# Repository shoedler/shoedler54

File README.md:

> Kailh Choc v2 Ice Creams, Taihao THTs

# shoedler54
A 54-key, column-staggered, ortholinear, wireless split keyboard, inspired by ZSA Voyager and silakka54.
Designed for Mx-spacing (18mm keycaps) and 1350 Choc v1 or v2 switches.

## Why?

This project came to life as I wanted to get up to speed with [ergogen.xyz](ergogen.xyz). The main goal of was to build a keyboard using solely the declarative ergogen paradigm - including making a case. As such, the only thing that was done outside of ergogen was to route the PCB and flip one case half in the slicer. That, as well as configuring the firmware (it'd be a nice extension to ergogen to generate the `.dtsi` file for ZMK automatically, but alas, that's not supported - yet).
Other things I've aimed for:
- Must be cheap, < $100 for a complete keyboard.
- Must be low profile, comparable to the ZSA Voyager.

## Impressions

> Carry case

> With optional MCU + battery cover

> Black version with Kailh Choc v2 Black Clouds, Repo-included 3D printed keycaps

---

## Bill of materials

For one complete board - e.g. two halves - you'll need:

- 2 Promicro NRF52840
- 54 1N4148W SOD-123 Diodes
- 54 Kailh Low-profile 1350 Hotswap Sockets
- 54 Keyswitches, Choc v1 or v2
- 54 1u (18mm) Keycaps, Choc v1 or v2 stems (I suggest to print the provided ones (Mx-stem e.g. Choc v2), or - if you want legends, the Taihao THTs)
- 2 EVQPUL02K Switches ($\to$ board reset button)
- 2 SSSS811101 Switches ($\to$ power switch)
- 2 801540 3.7v, 380mAh Batteries
  - or, 2 701535 3.7v, 350mAh
  - or, 2 501646 3.7v, 380mAh (these are too long (46mm) and require to be soldered to the JST pads, which I **do not recommend**!)
- 2 JST PH 2.0 THT Sockets

For the case you'll need:

- Obviously, the printed case files. See section about printing below.
- 10x M2x5 (or 6)mm flathead screws
- 10x M2x3mm Heat set inserts
- Optionally, some painters tape.

## Approximate cost

| What | Supplier | Comment | Price |
| --- | --- | --- | --- |
| 2 PCBs | JLCPCB | 5pcs. (min), including a hefty delivery fee to get to my location, $32 | ~$13 |
| 2 MCUs | AliExpress | Promicro NRF52840 | ~$4 |
| 54 Diodes | AliExpress | 1N4148W SOD-123 | ~$1 |
| 54 Kailh Low 1350 Sockets | AliExpress | Hotswap | $4 |
| 54 Keyswitches, Choc v1/v2 | AliExpress | pack of 70 | $25 |
| 54 1u Keycaps, Choc v1/v2 | AliExpress | pack of 60 | $15 |
| 2 Reset Switches | AliExpress | EVQPUL02K | ~$1 |
| 2 Power Switches | AliExpress | SSSS811101 | $1 |
| 2 Batteries | AliExpress | 801546, 380mAh | $8 |
| 2 JST PH 2.0 Sockets | AliExpress | | ~$1 |
> Prices as of january, 2026

Should result in ~$75 per completed keyboard. This does not include the case hardware and printed case files, but it's all you need to get a working keyboard. Also, the prices listed are adjusted to the amount of parts required.

> [!NOTE]
> You'd want to buy some parts in "bulk", like a strip of 100 diodes. Since you likely also have a minimum order quantity for the PCBs, it might make sense to buy two more MCUs and maybe some old keyswitches and caps to get another full keyboard out of the rest of the parts and still have one PCB for soldering mistakes left ;)

As alluded to in the BOM, a 3d printable model for a custom cap that fits this build is provided - more on that in the build guide.

## Build guide

### PCB manufacturing

> PCB related files are located in the `kicad` directory.

Assuming you have ordered the parts and don't want to route the PCB yourself, there's premade gerber archive located at `kicad/gerber.zip` which you can use. I've used JLCPCB, default settings (1.6mm two layer PCB) and with the black solder mask.

### Printing the case

> Case files are located in the `stl` directory.

I used a Babulab A1 mini and default slicer settings (Bambustudio). Everything was printed in their PLA Matte.

#### What do I need to print?

You'll need at least:

- 2x `shoedler54_switchplate_right.stl`, which is the plate that sits on the PCB and where the keyswitches are mounted into - I recommend using the provided 3mf files for that: `shoedler54_switchplate_left.3mf` and `shoedler54_switchplate_right.3mf`. That'll give you mirrored versions so you have the buildplate-finish texture on the same side for both halves.
- 2x `shoedler54_case_left.stl`, which is the case where the PCB gets mounted in - same story, use the provided 3mf files for that: `shoedler54_case_left.3mf` and `shoedler54_case_right.3mf`. That'll also give you mirrored versions for both halves with fuzzy skin. Theoretically, you don't **need** the case, but I strongly recommend it to provide a little bit of protection for the PCB. If you're working directly with the stl, then you'll have to mirror it. I suggest using the fuzzy skin setting (in Bambustudio: `Others > Special mode > Fuzzy skin`, use "Contour").

Optional:

- 2x `shoedler54_case_cover_right.stl`, which is a small cover for the MCU + battery. Use `shoedler54_case_cover_left.3mf` and `shoedler54_case_cover_right.3mf` for mirrored version. Same as with the case, if you're working with the stl directly you'll need to mirror this too.
- 1x `shoedler54_carry_case.stl`, which is a Go60-ish carry shell for the shoedler54. Use `shoedler54_carry_case.3mf` for a version with fuzzy skin. I did manage to print it without support, but there's a bit of luck involved.

### Printing the keycaps

> Keycap related files are located in the `scad` directory.

The caps require no supports if you place them on one of the fillets - they do however require good bed adhesion. This, just like the case, was also printed on a Bambulab A1 mini with PLA Matte. Also, like the case, I've provided a 3mf file to print 26 regular + 1 indexing (F/J keys on QWERTY) keys. If you have to use the stl directly:

- Use 0.12mm layer height (including the initial layer).
- Use a brim - if your slicer doesn't automatically generate it, add it manually.

> [!NOTE]
> The keycap was designed in [OpenSCAD](openscad.org). It's fully parametrized, so it's easy to adapt to your liking.

### Soldering

Since the PCB is reversible it can get confusing quick. All of the components **except the ProMicro and the JST connector** are soldered to the backside of each half.

1. Solder diodes, hotswap sockets, reset- and powerswitches on the backside of each half. **This is also the side were you bridge all of the solder-jumpers with solder** (8 for the Mcu, 2 for the Battery connector).
2. Direct-solder the ProMicro to the frontside of the PCB, along with the JST connector. (Pin Sockets are also an option for the mcu, if you want - it just makes the keyboard a bit thicker)

> [!CAUTION]
> Before you continue it's a good idea to verify that there's no short between the JSTs +/- terminal as well as the ProMicros VCC and GND.

I suggest to load the firmware next and check that everything works before assembly.

### Loading the ZMK firmware

> Firmware related files consist of: config/, boards/, zephyr/ directories, as well as the build.yml file and the GitHub Actions workflow in .github/workflows.build.yml

Get the latest firmware from https://github.com/shoelder/shoedler54/actions, select the latest run and scroll down to Artifacts - you'll be able to download the zip archive from there.

> [!NOTE]
> There'll be two .uf2 files per half in the zip archive - a `de-ch` and an `en` version. This refers to the keycode locale that's been used. I myself require a swiss locale, but, to make the default firmware more useful for more people, I've added an english version too. You can check the keymaps out in the `config/boards/shields/shoedler54` directory.

For each half:

1. Plug in the half to your device using a USB cable.
2. Press the reset button twice within 500ms - on my versions of the ProMicro, their red LED breaths gently once you've entered bootloader mode.
3. You'll see a `NICENANO` appear in your device tree. Simply drag and drop the **correct** firmware for the half your working on onto the mcu - it should eject itself automatically once the firmware is flashed.

> [!NOTE]
> If you run into trouble, there's also a `settings_reset` firmware provided in the archive. See [the ZMK troubleshooting guide](https://zmk.dev/docs/troubleshooting/connection-issues#reset-split-keyboard-procedure) on how to flash it.

### Assembly

1. Prep the cases by installing the heat set inserts.
2. Cover the bottom sides of the PCBs with tape (I used masking tape). Apply the first layer quite firmly, such that it follows the contours of the hotswap sockets. You'll want to make sure that you extend the tape over the edges of the PCB. Apply at least 3 layers. In my experience anything beyond 5 layers of standard painters tape yields no further improvements. Also, it gets thick quick.

3. Trace the PCB outline to the tape with a pen. Also, trace the screw holes.

4. Remove the tape, and cut out the shape - make sure to inset the cut about 2-3mm, so the tape is not visible when everything is assembled. For the screw holes, cut a ~5x5mm square. Apply the tape.

5. Assemble both halves.

6. Install the switches, caps and the battery. For the battery, I usually use a thin, clear double-sided tape. Done!

---

## Modifying the ergogen config

The whole point of using ergogen, is to easily adapt the PCB to your liking. So give it a go!
Modifying the config will force you to reroute the PCB again. Though fear not - using [Freerouting](www.freerouting.app) this literally takes a minute to do (including adding freerouting to KiCad), provided you have KiCad >=8 and JRE >= 17 for Freerouting already installed.

> [!NOTE]
> To add the Freerouting KiCad integration, just follow [this](https://github.com/freerouting/freerouting/blob/master/docs/integrations.md) official guide.

1. Paste `config.yml` located in `/ergogen` into [ergogen.xyz](ergogen.xyz) and download the `shoedler54.kicad_pcb` file.
2. Copy (and overwrite) `shoedler54.kicad_pcb` to the `kicad` directory of this repository *(this part is only required if you intend to keep the source of this repository up to date - e.g. if you forked this)*
3. Open the PCB in KiCad (Standalone PCB editor suffices) and click on `Tools > External Plugins > Freerouting`
4. Let it rip. In my experience, the defaults of Freerouting suffice.

> [!IMPORTANT]
> Back in KiCad, run the DRC in `Inspect > Design Rule Checker`. I usually right click `> Ignore all 'Footprint not found in libraries' violations` to ignore missing ceoloide footprint warnings. This might leave you with some warnings which you need to manually resolve. For example, i usually get "Track has unconnected end", which is easily resolved by deleting the stub.

5. `File > Plot... > Generate Drill Files`, name the folder "gerber", then press `Generate` and close that popup. Press `Plot` back in the plot dialog. Done!

## References

- Flatfootfox' detailed design guide: https://flatfootfox.com/ergogen-part1-units-points/
- nickcoutsos Keymap-editor: https://nickcoutsos.github.io/keymap-editor/
- nickcoutsos Keymap-layout-tools: https://nickcoutsos.github.io/keymap-layout-tools/
- Joel Spadins zmk-locale-generator for the de-swiss keycode header: https://github.com/joelspadin/zmk-locale-generator
- ZMK guide on how to add a new shield: https://zmk.dev/docs/development/hardware-integration/new-shield
- More of my keyboards:
  - effiddy - a 50-key wireless split, inspired by totem: https://github.com/shoedler/effiddy
  - ezy54 - A 54-key, column-staggered, wireless split keyboard, inspired by ZSA Voyager and totem: https://github.com/shoedler/ezy54

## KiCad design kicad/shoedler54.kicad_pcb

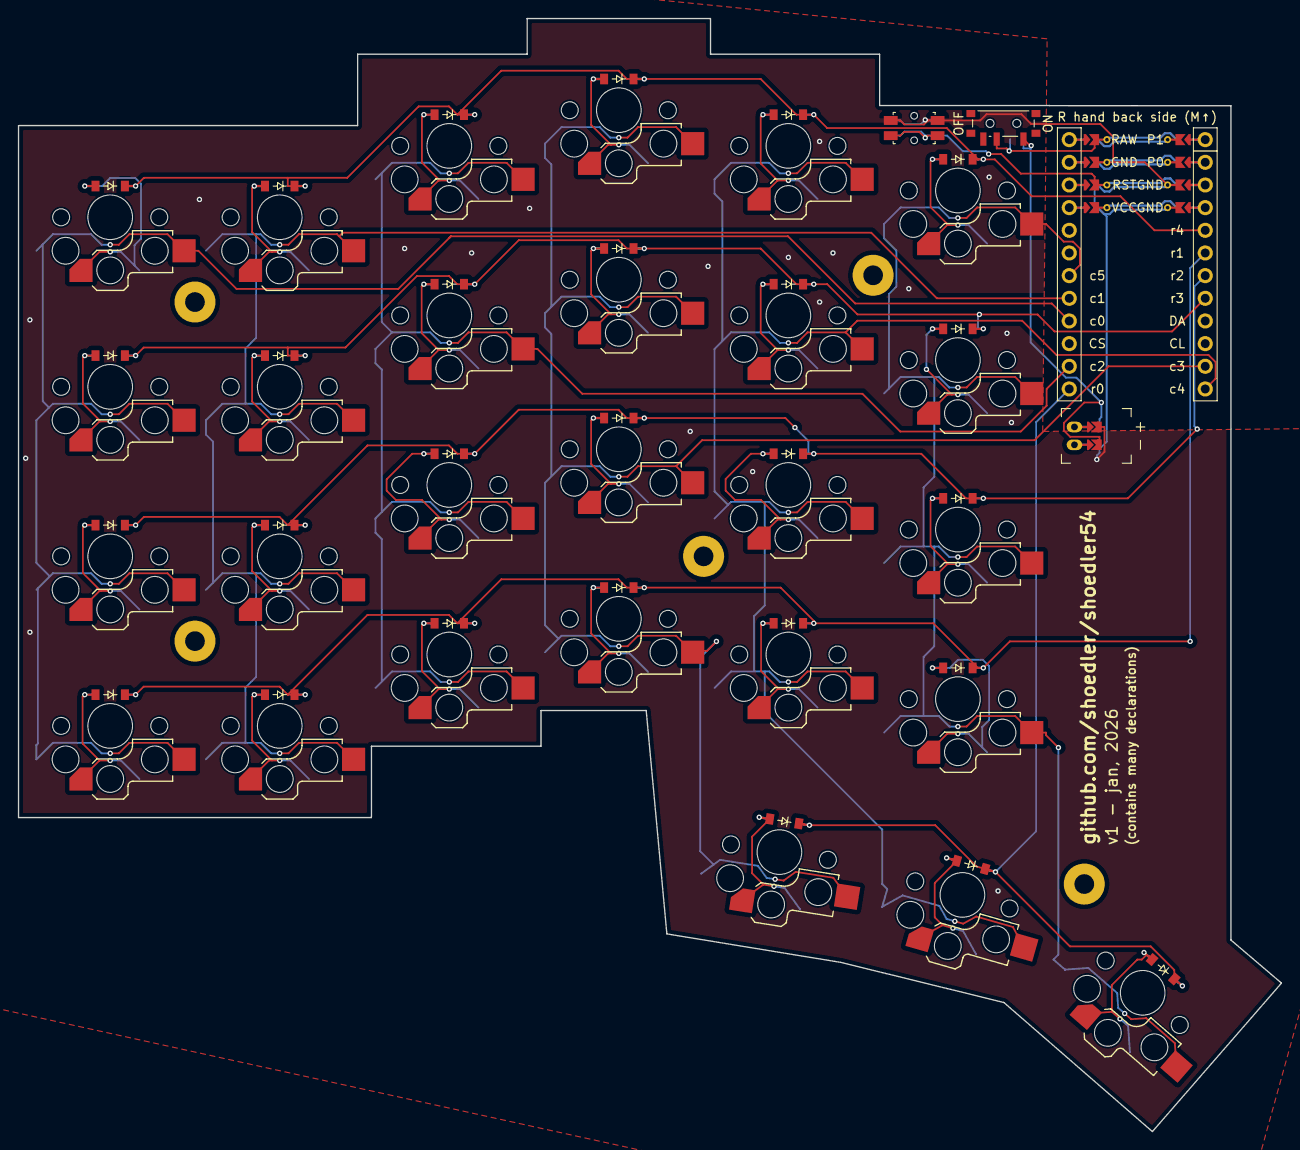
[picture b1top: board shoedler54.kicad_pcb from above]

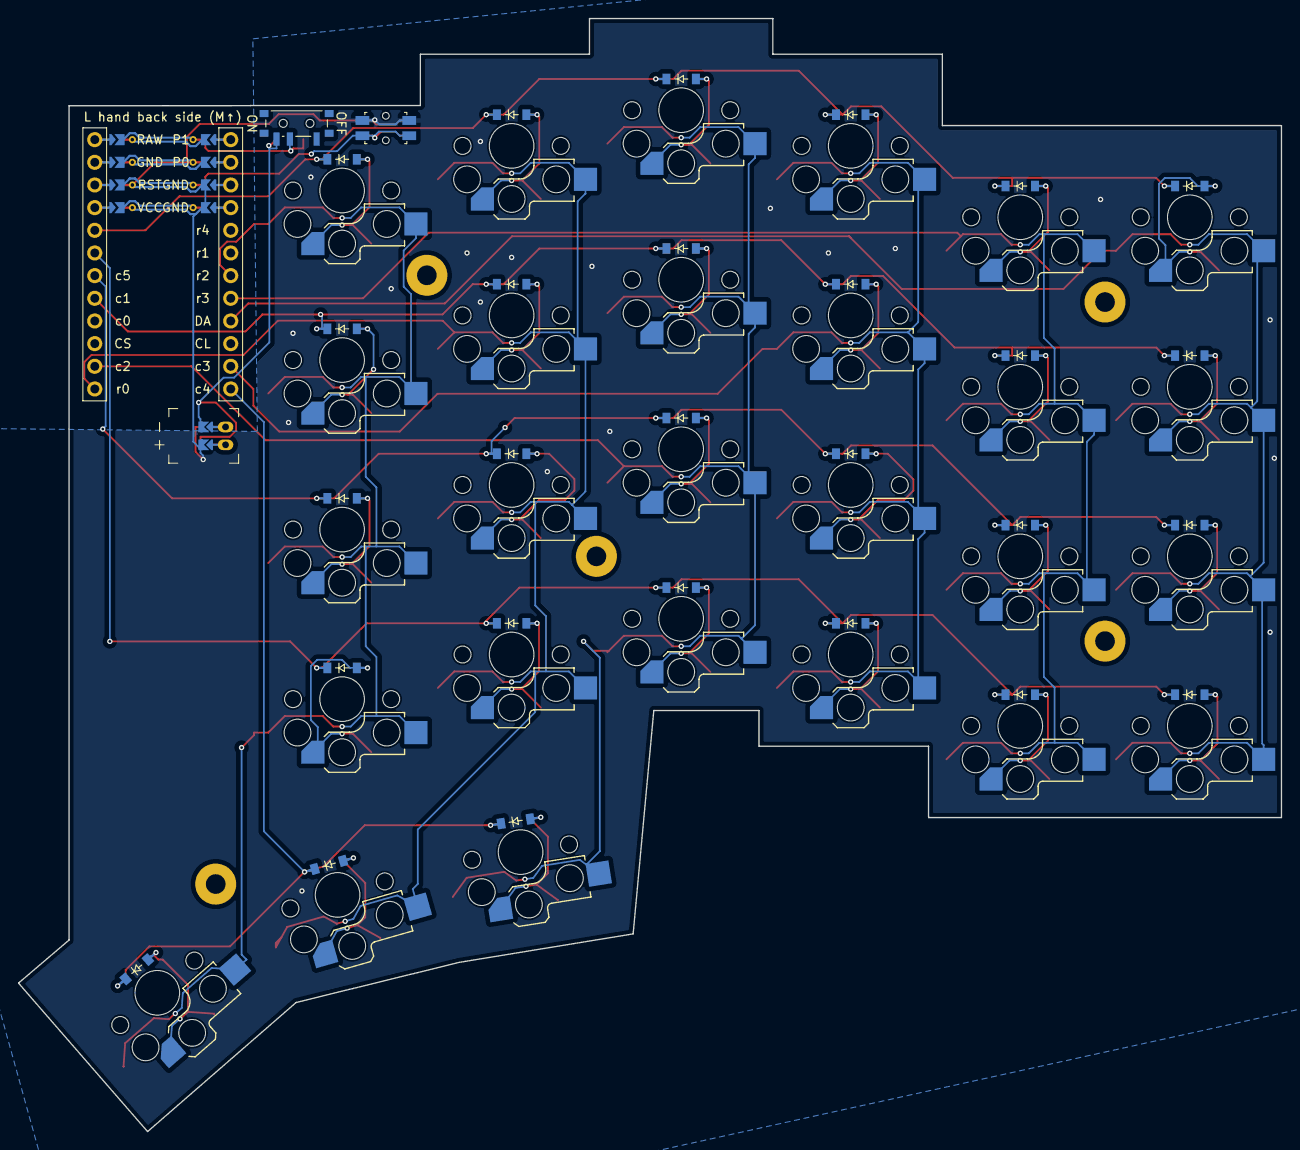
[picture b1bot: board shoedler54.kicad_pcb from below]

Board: 2 copper layers, 141.5 x 124.7 mm, 63 parts (27 on the bottom side), 44 nets.

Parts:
D1, D2, D3, D4, D5, D6, D7, D8, D9, D10, D11, D12, D13, D14, D15, D16, D17, D18, D19, D20, D21, D22, D23, D24, D25, D26, D27: diode_tht_sod123
JST1: battery_connector_jst_ph_2
MCU1: mcu_supermini_nrf52840
MH1, MH2, MH3, MH4, MH5: mounting_hole_npth
PWR1: power_switch_smd_side
RST1: reset_switch_smd_side
S1, S2, S3, S4, S5, S6, S7, S8, S9, S10, S11, S12, S13, S14, S15, S16, S17, S18, S19, S20, S21, S22, S23, S24, S25, S26, S27: switch_choc_v1_v2

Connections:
BAT_P: JST1.1, PWR1.1, PWR1.3
GND: JST1.2, MCU1.103, MCU1.104, MCU1.123, RST1.1, RST1.3
JST1_1: JST1.11, JST1.21, JST1.31
JST1_2: JST1.12, JST1.22, JST1.32
RAW: MCU1.124, PWR1.2
RST: MCU1.122, RST1.2, RST1.4
c0: MCU1.16, S1.2, S2.2, S3.2, S4.2
c0_r1: D1.2, S1.1
c0_r2: D2.2, S2.1
c0_r3: D3.2, S3.1
c0_r4: D4.2, S4.1
c1: MCU1.17, S5.2, S6.2, S7.2, S8.2
c1_r1: D5.2, S5.1
c1_r2: D6.2, S6.1
c1_r3: D7.2, S7.1
c1_r4: D8.2, S8.1
c2: MCU1.14, S9.2, S10.2, S11.2, S12.2
c2_r1: D9.2, S9.1
c2_r2: D10.2, S10.1
c2_r3: D11.2, S11.1
c2_r4: D12.2, S12.1
c3: MCU1.11, S13.2, S14.2, S15.2, S16.2, S25.2
c3_r0: D25.2, S25.1
c3_r1: D13.2, S13.1
c3_r2: D14.2, S14.1
c3_r3: D15.2, S15.1
c3_r4: D16.2, S16.1
c4: MCU1.12, S17.2, S18.2, S19.2, S20.2, S26.2
c4_r0: D26.2, S26.1
c4_r1: D17.2, S17.1
c4_r2: D18.2, S18.1
c4_r3: D19.2, S19.1
c4_r4: D20.2, S20.1
c5: MCU1.18, S21.2, S22.2, S23.2, S24.2, S27.2
c5_r0: D27.2, S27.1
c5_r1: D21.2, S21.1
c5_r2: D22.2, S22.1
c5_r3: D23.2, S23.1
c5_r4: D24.2, S24.1
r0: D25.1, D26.1, D27.1, MCU1.13
r1: D1.1, D5.1, D9.1, D13.1, D17.1, D21.1, MCU1.6
r2: D2.1, D6.1, D10.1, D14.1, D18.1, D22.1, MCU1.7
r3: D3.1, D7.1, D11.1, D15.1, D19.1, D23.1, MCU1.8
r4: D4.1, D8.1, D12.1, D16.1, D20.1, D24.1, MCU1.5

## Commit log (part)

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2026-01-08 Enhance ergogen.yml for KiCad integration
2026-01-08 Move to local ergogen
2026-01-09 Removes output, fixes row/col net
2026-01-09 Revise ergogen, start pcb tracing
2026-01-14 Adds initial case def
2026-01-14 Adds v2 for v1 prototype findings
2026-01-15 Updates README, makes v1 deprecated, removes ceoloide footprint dependency
2026-01-15 Fixes typo
2026-01-15 Moves deprecates/outdates v1 files - currently no v2 files exists, as there might be more findings
2026-01-15 Updates README
2026-01-17 Adds zmk
2026-01-21 Removes firmware
2026-01-21 Updates README and adds case to ergogen config (left only)
2026-01-21 Removes deprecated files and adds new PCB and case files
2026-01-21 Adds initial firmware
2026-01-21 Update build.yml (trying to cheese 'yq')
2026-01-21 Moves firmware files to repo root
2026-01-22 Fixes zmk physical layout, updates keymap and README
2026-01-22 Removes stale unicode ref
2026-01-22 Fixes include
2026-01-22 Adds fw name
2026-01-23 Updates case files
2026-01-24 Updates keymap for de-CH locale
2026-01-24 Fixes keymap
2026-01-25 Adds keycap files
2026-01-25 Fixes keycap indexing location
2026-01-25 Adds en keymap - just de-ch isn't useful for many people. lol.
2026-01-25 Fixes keymap includes
2026-01-25 Moves keymap files
2026-01-25 Moves header
2026-01-26 Adds bt bindings to de-ch keymap
2026-01-26 Adds bt bindings to en keymap
2026-01-26 Updates keymaps, added L3 for bt connections, replaced &khkp with mt
2026-01-26 Fixes keymap typo
2026-01-26 Fixes typo in en keymap
2026-01-27 Update README.md
    Fixes typo
2026-01-27 Adds tap-preferred mt variant for umlauts.
2026-01-27 Fixes mttp behavior
2026-02-04 Fixes PCB silkscreen text, as JLCPCB fears having ergogen.xyz on it will trouble the customs paw patrol. Also made GND fill zones better by adding some vias.
2026-02-04 Refactors ergogen config (Outputs are unaffected), renames printables, updates README accordingly.
2026-02-04 Refactors ergogen config (Outputs are unaffected)
2026-02-04 Updates keycap and its printfile to better match a similar off the shelf cap...
2026-02-04 Updates README.md
2026-02-05 Fixes browser back + fwd, makes bspc (l-shift hold) tap preferred.
2026-02-16 Fixes keymap formatting
2026-02-16 Adds reset firmware.
2026-02-19 Adds quick tap to bspc for repeats.
2026-02-19 Adds missing scolon.
2026-02-19 Updates timings.
2026-04-08 Adds supports to carry case 3mf
2026-04-22 Adds keymap image gen tool
